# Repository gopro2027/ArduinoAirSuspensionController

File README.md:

# Open Air Suspension Management (OAS-Man)
 
<!----->

###  [  Please click here to join the Discord server](https://discord.gg/pUf7FmHKpg) 
###  [  Click here to view the comprehensive build tutorial and documentation!](https://oasman.dev)
###  [  Click here for the oasman installer/update page](https://oasman.dev/flash)

### Important Info To Potential Creators:
Please join the discord for more specific information before you built it!<br>
There may be important information to share before you begin purchasing parts.<br>

### Overview:
This is intended as a DIY replacement for products such as Airlift 3P/3H ($1500) or Airtek Stage 2+ ($1000) with a build cost of less than $500. Combined with the customizability of open sourced code, I hope this is a tempting option for some DIY-ers out there.<br>
Our goal with this project is to provide the car community with a modern fully customizable well documented air suspension system with a budget build cost in mind, all not bound by the limitations of a single company. The rest of your car is custom to you, why not your air suspension too?<br>
- Want to customize the app to match your ride? You got it.<br>
- Did your proprietary air suspension software stop working and there's no update? Not an issue here!<br>
- Sensor broke in your proprietary manifold and you have to buy a whole new one for $1000? Not an issue here, just replace the sensor for $10.<br>
- Want to use bespoke heavy duty valves but also have a nice user interface? Look no further than OAS-Man!<br>
- Control your system with a PS3/PS4/Xbox controller? Yep, [we have that](https://www.youtube.com/shorts/fbXJVwzc6P0)<br>
- Restomodding an old air suspension system? OAS-Man may be the solution!<br>
- Literally any idea you've ever wanted to try with air suspension? OASMan is the best place to start.<br>

This github repo includes an android app<sup>1</sup> and esp32 code along with some 3d printable files and a PCB. The PCB is pre-made SMD and ready for upload in JLCPCB with assembly so minimal-to-no soldering required. There is also a pre-made touch screen device you can order ($25 to $40) which is used as the dedicated controller<sup>2</sup>. There is an easy to use webpage to upload the software so there is no coding required. You will still need to supply the rest of your system which is not covered in this project, such as struts/bags, tank, compressor, tubing and fittings, ect. So that is what you would need in addition to this, similarly to what you would need for one of the on-the-shelf manifolds. If you are unsure what to purchase, I suggest referencing (or purchasing!) the [Airtekk Stage 1 Kit](https://www.airtekk.com/product-p/uni-stage1-kit.htm) as that will just about cover everything you need.<br>
<sub>1. The mobile app is behind on development and lacks various features of the controller software, and currently only has an android release. Recommended to use the touch screen controller for full functionality.</sub><br>
<sub>2. Please view the tutorial and build instructions for more info.</sub>

### Branch Information:
**main branch = ESP32** (Current full version of OASMan)<br>
**dev branch = ESP32** (Bleeding edge updates to OASMAN)<br>
**nano-v1 branch = Arduino Nano** (outdated, no longer maintained, only exists for legacy purposes)<br>
**Other branches = current dev work** (Other dev work which you can ignore)<br>
<br>
### Folder Information:
**tutorial** - Contains important build instructions (must read)<br>
**OASMan_ESP32** - The main board project<br>
**Wireless_Controller** - The project for the wireless controller of the main board<br>
**builds** - Mobile App Builds (apk's ect)<br>
**ESP32_SHARED_LIBS** - Contains files used between the main board and controller projects. Notably the config file which you may or may not need to edit.<br>
**LCDImageCreatorTool** - Code generator for making images for the tiny 128x64 screen on the manifold.<br>
**MobileApp** - New flutter mobile app using BLE (incomplete at the time of this writing)<br>
**3d Prints** - Contains files for 3d printing (more info in tutorials)<br>
**PCB** - PCB files. More info in tutorial<br>
**PS3_Controller_Tool** - Contains instructions & exe for setting the MAC address of your ps3 controller to work with OASMan<br>
**photos** - photos<br>
<br>

<br>

<!---
**Loose steps:** <br>
1. Order parts, order circuit board on JLPCB website, 3d print parts
2. Solder parts to circuit board, flip all switches to off
    1. For the manifold connector, wire the white wires (abcdefgh) in alphabetical order on the board, so 1 is a, 2 is b, and so on. The 9th wire goes to the spot right above the rest of the wires.
    2. The pressure sensors go in order... 1(manifold) -> FP (board) ... 4 -> RD. In general the order of everything is FRONT PASSENGER, REAR PASSENGER, FRONT DRIVER, REAR DRIVER abbreviatted FP, RP, FD, RD, sorry for the odd order it happened by accident
4. Configure code:
    1. get mac address of HC-06 bluetooth device by using an app or sommething to find it.
    2. Put the mac address in the android code, replacing the old mac address
    3. (Optional) Update the passwords in the app and arduino code if you want
    4. Write code to arduino
5. Circuit board single switch off, on the double switch make the top one on and bottom one off (this will power the arduino by 5v from the buck converter. 12 is bottom switch if you want to use that instead but you can ignore it)
-->

<!--

-->
<!---->
<!---->

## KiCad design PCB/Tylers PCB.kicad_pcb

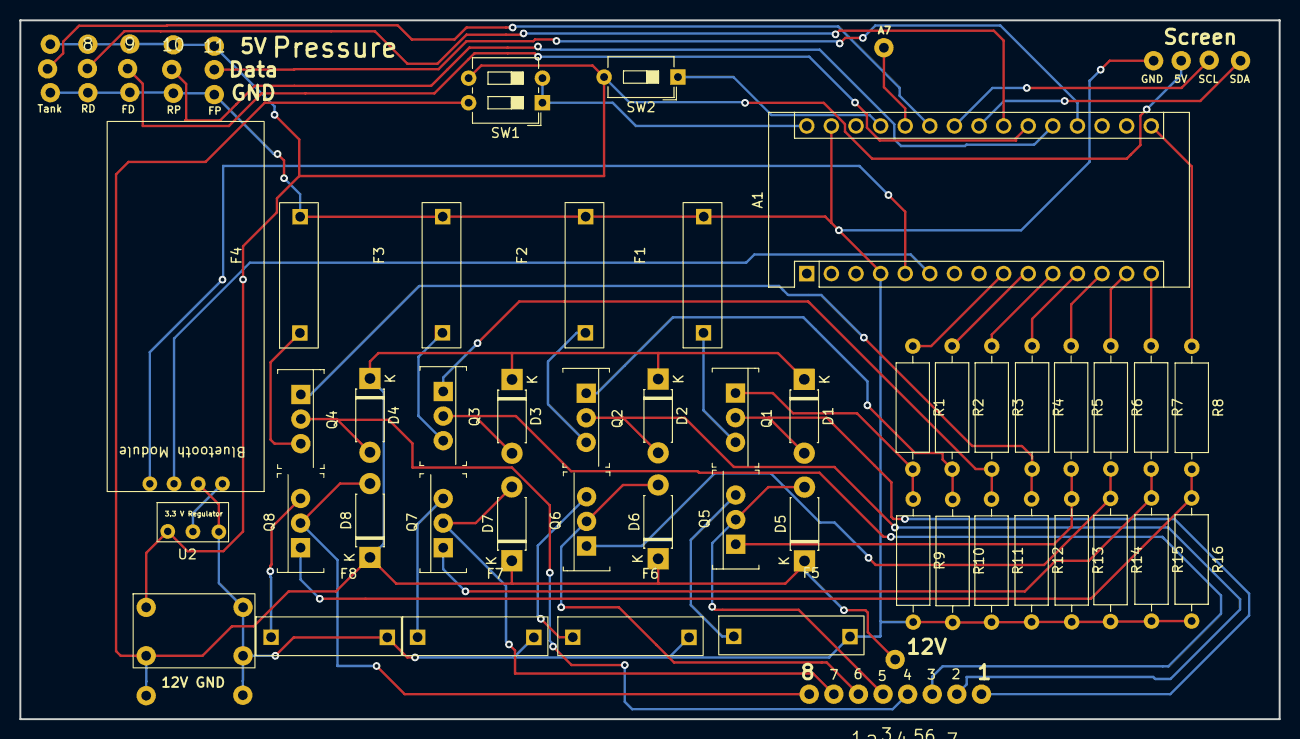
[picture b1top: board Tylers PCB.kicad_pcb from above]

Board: 2 copper layers, 130.0 x 72.1 mm, 62 parts (0 on the bottom side), 40 nets.

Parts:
1, 2, 3, 4, 5, 6, 7, 8, 9, 10, 11, 12, 13, 14, 15, 16: (no value)
3.3 V Regulator: 3.3V_regulator; 3.3V regulator
A1: Arduino_Nano_v3.x; Arduino_Nano
Bluetooth Module: DSD_Tech_Bluetooth_Module; DSD Tech Bluetooth Module
D1, D2, D3, D4, D5, D6, D7, D8: 1N4007; D_DO-41_SOD81_P7.62mm_Horizontal
F1, F2, F3, F4, F5, F6, F7, F8: 3A Fuse; 3.6x10mm
Q1, Q2, Q3, Q4, Q5, Q6, Q7, Q8: FQP30N06L; TO-220-3
R1, R2, R3, R4, R5, R6, R7, R8: R150; R_Axial_DIN0309_L9.0mm_D3.2mm_P12.70mm_Horizontal
R9, R10, R11, R12, R13, R14, R15, R16: R10K; R_Axial_DIN0309_L9.0mm_D3.2mm_P12.70mm_Horizontal
SW1: SW_DIP_x02; SW_DIP_SPSTx02_Slide_6.7x6.64mm_W7.62mm_P2.54mm_LowProfile
SW2: SW_DIP_x01; SW_DIP_SPSTx01_Slide_6.7x4.1mm_W7.62mm_P2.54mm_LowProfile
U2: DIY_More_Buck_Converter; DIY More Buck Converter

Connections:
+12V: D1.1 (K), D2.1 (K), D3.1 (K), D4.1 (K), D5.1 (K), D6.1 (K), D7.1 (K), D8.1 (K), SW1.4, U2.2 (12V_IN)
GND: 3.3 V Regulator.3 (GND), 12.1, 13.1, 14.1, 15.1, 16.1, A1.4 (GND), A1.29 (GND), Bluetooth Module.3 (GND), F1.2, F2.2, F3.2, F4.2, F5.2, F6.2, F7.2, F8.2, R9.2, R10.2, R11.2, R12.2, R13.2, R14.2, R15.2, R16.2, U2.1 (GND_IN), U2.3 (GND_OUT)
unnamed: A1.5 (D2), Bluetooth Module.1 (RX0)
unnamed: A1.6 (D3), Bluetooth Module.2 (TX0)
unnamed: A1.9 (D6), R1.1
unnamed: A1.10 (D7), R2.1
unnamed: A1.11 (D8), R3.1
unnamed: A1.12 (D9), R4.1
unnamed: A1.13 (D10), R5.1
unnamed: A1.14 (D11), R6.1
unnamed: A1.15 (D12), R7.1
unnamed: A1.16 (D13), R8.1
unnamed: A1.27 (+5V), SW2.1
unnamed: A1.30 (VIN), SW1.1, SW1.2
unnamed: F1.1, Q1.3 (S)
unnamed: F2.1, Q2.3 (S)
unnamed: F3.1, Q3.3 (S)
unnamed: F4.1, Q4.3 (S)
unnamed: F5.1, Q5.3 (S)
unnamed: F6.1, Q6.3 (S)
unnamed: F7.1, Q7.3 (S)
unnamed: F8.1, Q8.3 (S)
unnamed: Q1.1 (G), R1.2, R9.1
unnamed: Q2.1 (G), R2.2, R10.1
unnamed: Q3.1 (G), R3.2, R11.1
unnamed: Q4.1 (G), R4.2, R12.1
unnamed: Q5.1 (G), R5.2, R13.1
unnamed: Q6.1 (G), R6.2, R14.1
unnamed: Q7.1 (G), R7.2, R15.1
unnamed: Q8.1 (G), R8.2, R16.1
unnamed: 3.3 V Regulator.1 (VIN), 8.1, 9.1, 10.1, 11.1, SW1.3, SW2.2, U2.4 (5V_OUT)
unnamed: 3.3 V Regulator.2 (VOUT), Bluetooth Module.4 (VIN)
To Solenoid 1: 7.2 (D), D1.2 (A), Q1.2 (D)
To Solenoid 2: 6.2 (D), D2.2 (A), Q2.2 (D)
To Solenoid 3: 5.2 (D), D3.2 (A), Q3.2 (D)
To Solenoid 4: 4.2 (D), D4.2 (A), Q4.2 (D)
To Solenoid 5: 3.2 (D), D5.2 (A), Q5.2 (D)
To Solenoid 6: 2.2 (D), D6.2 (A), Q6.2 (D)
To Solenoid 7: 1.2 (D), D7.2 (A), Q7.2 (D)
To Solenoid 8: D8.2 (A), Q8.2 (D)

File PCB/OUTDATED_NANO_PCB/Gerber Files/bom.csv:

Designator,Footprint,Quantity,Value,LCSC Part #
15,,1,,
7,,1,,
F2,3.6x10mm,1,3A Fuse,
Q4,TO-220-3,1,FQP30N06L,FQP30N06L
13,,1,,
R1,R_Axial_DIN0309_L9.0mm_D3.2mm_P12.70mm_Horizontal,1,R150,
3.3 V Regulator,3.3V regulator,1,3.3V_regulator,
12,,1,,
_15,,1,,
9,,1,,
R4,R_Axial_DIN0309_L9.0mm_D3.2mm_P12.70mm_Horizontal,1,R150,
R14,R_Axial_DIN0309_L9.0mm_D3.2mm_P12.70mm_Horizontal,1,R10K,
Bluetooth Module,DSD Tech Bluetooth Module,1,DSD_Tech_Bluetooth_Module,
R8,R_Axial_DIN0309_L9.0mm_D3.2mm_P12.70mm_Horizontal,1,R150,
D2,D_DO-41_SOD81_P7.62mm_Horizontal,1,1N4007,
SW1,SW_DIP_SPSTx02_Slide_6.7x6.64mm_W7.62mm_P2.54mm_LowProfile,1,SW_DIP_x02,
R7,R_Axial_DIN0309_L9.0mm_D3.2mm_P12.70mm_Horizontal,1,R150,
_14,,1,,
D5,D_DO-41_SOD81_P7.62mm_Horizontal,1,1N4007,
R2,R_Axial_DIN0309_L9.0mm_D3.2mm_P12.70mm_Horizontal,1,R150,
Q8,TO-220-3,1,FQP30N06L,FQP30N06L
16,,1,,
_13,,1,,
D6,D_DO-41_SOD81_P7.62mm_Horizontal,1,1N4007,
F7,3.6x10mm,1,3A Fuse,
R5,R_Axial_DIN0309_L9.0mm_D3.2mm_P12.70mm_Horizontal,1,R150,
6,,1,,
U2,DIY More Buck Converter,1,DIY_More_Buck_Converter,
_12,,1,,
2,,1,,
R16,R_Axial_DIN0309_L9.0mm_D3.2mm_P12.70mm_Horizontal,1,R10K,
A1,Arduino_Nano,1,Arduino_Nano_v3.x,
R15,R_Axial_DIN0309_L9.0mm_D3.2mm_P12.70mm_Horizontal,1,R10K,
_11,,1,,
F3,3.6x10mm,1,3A Fuse,
_10,,1,,
_9,,1,,
R10,R_Axial_DIN0309_L9.0mm_D3.2mm_P12.70mm_Horizontal,1,R10K,
_8,,1,,
_7,,1,,
8,,1,,
Q7,TO-220-3,1,FQP30N06L,FQP30N06L
SW2,SW_DIP_SPSTx01_Slide_6.7x4.1mm_W7.62mm_P2.54mm_LowProfile,1,SW_DIP_x01,
3,,1,,
F8,3.6x10mm,1,3A Fuse,
10,,1,,
11,,1,,
R11,R_Axial_DIN0309_L9.0mm_D3.2mm_P12.70mm_Horizontal,1,R10K,
4,,1,,
D3,D_DO-41_SOD81_P7.62mm_Horizontal,1,1N4007,
F4,3.6x10mm,1,3A Fuse,
_6,,1,,
F1,3.6x10mm,1,3A Fuse,
D7,D_DO-41_SOD81_P7.62mm_Horizontal,1,1N4007,
F5,3.6x10mm,1,3A Fuse,
_5,,1,,
R6,R_Axial_DIN0309_L9.0mm_D3.2mm_P12.70mm_Horizontal,1,R150,
D8,D_DO-41_SOD81_P7.62mm_Horizontal,1,1N4007,
_4,,1,,
D1,D_DO-41_SOD81_P7.62mm_Horizontal,1,1N4007,
R3,R_Axial_DIN0309_L9.0mm_D3.2mm_P12.70mm_Horizontal,1,R150,
R13,R_Axial_DIN0309_L9.0mm_D3.2mm_P12.70mm_Horizontal,1,R10K,
_3,,1,,
Q6,TO-220-3,1,FQP30N06L,FQP30N06L
Q3,TO-220-3,1,FQP30N06L,FQP30N06L
5,,1,,
Q5,TO-220-3,1,FQP30N06L,FQP30N06L
_2,,1,,
R9,R_Axial_DIN0309_L9.0mm_D3.2mm_P12.70mm_Horizontal,1,R10K,
D4,D_DO-41_SOD81_P7.62mm_Horizontal,1,1N4007,
Q2,TO-220-3,1,FQP30N06L,FQP30N06L
,,1,,
F6,3.6x10mm,1,3A Fuse,
1,,1,,
14,,1,,
R12,R_Axial_DIN0309_L9.0mm_D3.2mm_P12.70mm_Horizontal,1,R10K,
Q1,TO-220-3,1,FQP30N06L,FQP30N06L

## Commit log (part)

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2026-01-24 Undid some comment changes that shouldn't have been comitted
2026-01-24 Cleaned up unnecessary changes in ws2p8b and ws3p5b
2026-01-24 Fix whitespace in 2p8b
2026-01-24 Moved createModernNavbar to private
2026-01-25 Removed unnecessary code that blocked -1 from clearing the selected icons
2026-01-25 reinit update for controls
    updated manual controls to work with rotation and color changes.
2026-01-25 Proper cleanup update
    Each screen properly cleans up its own objects
    ui_reinit() is clean and simple (just 3 cleanup calls)
    Adding new Options only requires updating that screen's code
2026-01-25 Made valve code better. Temporarily fixed arrows rendering
2026-01-25 Fixed memory leak with pill arrows
2026-01-25 Fixed memory leak with pill divider points
2026-01-25 Added theme color desert sand
2026-01-25 Fix for arrows looking funny
2026-01-26 removed unused code
    removed legacy control code
2026-01-26 Weird thing with ui_updateBtn
2026-01-26 Added a bit extra safety to the option class even though unnecessary
2026-01-26 Fixed animation for 2p8b by adding LV_USE_STDLIB_MALLOC=LV_STDLIB_CLIB
2026-01-26 Changed 2p8b to be double buffered partial render
2026-01-26 Cleaned up duplicate code on ui_scrPresets.cpp
2026-01-28 Removed unused ui helpers
2026-01-29 Fix for navbar callbacks
2026-01-29 added animated navbar underline
2026-01-30 update for statusbar information
2026-01-30 Added led code
2026-02-03 New car creator program
2026-02-03 More updates to custom car image maker
2026-02-03 Made the program better
2026-02-03 Reverted formatting changes because I know it's gonna give us some merge conflicts later if I don't
2026-02-05 Added manifold decorative plate
2026-02-06 Update for statusbar/Post-reload
    Added new brightness_slider_released_cb that calls setbrightness()
    Added bool animate = true parameter to changeScreen() (default preserves existing behavior)
    ui_reinit() now calls changeScreen(prevScreen, false) — instant page switch after reload
2026-02-11 Removed some laggy animations
    status bar dropdown and pill resizing
2026-02-19 Turn off 6 valve manifold
2026-02-19 Changed color to dark cyan
2026-02-20 Added adsD and auto switch tank sensor to it if it exists
2026-02-20 Added isVehicleParked function
    GPS code for it isn't finished yet though, but I will use this function to update other features safety.
2026-02-20 Implemented isVehicleParked in a few spots where it was needed
    Still need to implement isVehicleParked on the videogame controller
2026-02-21 Fixed car rendering position
2026-02-21 Fixed 2.8b backlight
2026-02-21 added SIX_VALVE_MANIFOLD_OPEN_TANK_VALVE_WHEN_COMPRESSOR_IS_RUNNING
    Should only be used as directed in the user_defines.h
2026-03-01 First pass of code, need to test and clean up bugs
2026-03-01 Bug on frontend didn't set default value of on off properly
2026-03-02 Hide height sensor toggleable values when not selected
2026-03-02 magic number wheel nums
2026-03-02 Initial cleanup of these status packets into a config bittset
    Hasn't been tested yet at all. Needs testing of all 6 of these functions before it can be moved along.
2026-03-02 Updated gfx library version to 1.6.5 in hopes it fixed the incompatability with latest version of arduino-esp32
    I'm not entirely sure why it's downloading a new version of arduino esp32 and not using a fixed verssion, but not looking into that right now. Here is a github issue of the error for reference: https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
2026-03-02 Fix for new core version in nimble
2026-03-06 Fix for six valve manifold to force the compressor (and tank valve) off when tank output is opened
2026-03-06 Updated mobile app with new bluetooth code
2026-03-06 Initial commit. Has some UI issues
2026-03-29 Auxillary code WIP NOT FINISHED
    Should have the first few functions working on timing
    have not added anything to the controller side yet.
    Needs changed to be a bittset of functions that are stored, and the first 2 manual functions are called statefully instead of being stored as a setting.
2026-03-29 removed device libs from search exclude
2026-04-02 Added initial upload for knob device support
    https://www.waveshare.com/wiki/ESP32-S3-Knob-Touch-LCD-1.8
2026-04-02 First version of settings for circle screen ui
2026-04-02 Okay finished first ui for circle screen.
2026-04-03 Home screen circle glow
2026-04-03 Removed glow and replaced with simple color change
2026-04-03 Slight speed improvement in circular screen driver. Changes partial lines flush to 24 from 16 and 20
2026-04-03 Updates to preset page
2026-04-03 Moved preset button to center of home screen
2026-04-03 Updates to the UI on the home page with the preset button
2026-04-03 Fixed button press bug on air out, inverted arc so they all fill upwards
2026-04-03 added preset number to help with feedback when loading a new preset
    The preset would otherwise be 'hidden' so this helps at least show it if we swap to a different preset
2026-04-03 added the knob to the build
2026-04-03 Added rotary guage to the website
2026-04-05 Updated packet format in flutter app and made it save upon edit
    also updated the manifold so that in the config packet if i set the values, it will update all connected controllers
2026-04-05 Updated names of settings to match the controller
2026-04-05 Added more of the settings from the controller to the mobile app
2026-04-05 Fixed direct download when proxy is rate limited
    This fixes the -5 error i was getting at times.
    Summary of fix:
    Moved wificlientsecure to global scope. https stores a copy of this object, so wanted to make sure it sticks around
    Also make the https object into a pointer, so i can delete it to fix the later issue that happens if we try to reuuse https as http.
2026-04-05 Fixed slight typo
2026-04-05 Added a switch to go from stream to non-stream on json response
    Mainly because on the controller if we run on the github direct it sometimes responds in chunked format which the streamed version is not a fan of trying to parse, so then we retry with the non-strea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
2026-04-05 Added privacy policy to mobile app settings
2026-04-07 Temporary fix for 3.5 and update nimble to 2.5.0
2026-04-07 Clean up some of the unnecessary code on the statusbar
2026-04-07 undid a useless code change
2026-04-09 Moved auxillary output mode to config values packet and added manual control packet
2026-04-09 Added internal setting to auxillary output
2026-04-10 Removed detect pressure sensors, and fixed image picker permission bug
2026-04-10 Fixed app name and icon
2026-04-10 Fixed website link button
2026-04-10 Improved performance on settings page
2026-04-10 updated _readOnlyStatusRow to wrap gracefully
2026-04-14 Added deciseconds to auxillary output settings
2026-04-17 Improved setup code in the settings and added auxillary output page
2026-04-27 Removed commented out code
2026-05-15 Added auxillary settings to mobile app
2026-05-15 Fixed valve mask on axle up down mobileapp
2026-05-15 Fixed up down axle bug
2026-05-15 Added auxillary settings to mobileapp
2026-05-15 Fixed graphical error on selected item in settings dropdown on controller
2026-05-15 Fixed bug where you could click behind dialogs
2026-05-15 Disabled triangle icon in statusbar until we decide to wire it up to something more important
2026-05-15 Made oled screen address save into nvs for people with odd screen addresses
2026-05-17 4.0 Board update
    4.0 PCB complete update. Corrected zener and silk screen error.
2026-05-18 4.0.1 HotFix
    4.0 Board corrections updated to 4.0.1 HotFix
2026-05-18 Config packet issue fix
    Sometimes when saving a preset the config packet saves bad data from the stack to the board. This ensures that does not happen.
2026-05-19 Significantly simplified ota updates by moving almost all the code into the cloudflare worker
2026-05-19 Cloudflare worker will now delete the cache of all the binaries if a new release json version is found
2026-05-19 Fixed a bug with short overflow.
2026-05-19 Updated actions script to be compatable with node 24
    This is untested code. Github says june 2nd they are upgrading to node 24 though
2026-05-19 fix: V-001 security vulnerability
    Automated security fix generated by OrbisAI Security
2026-05-19 temporarily removed most for build test
2026-05-19 Revert "temporarily removed most for build test"
    This reverts commit 26e48c4e61cf8bbefe60280e41d3bee1b5e637a0.
2026-05-19 fix: V-006 security vulnerability
    Automated security fix generated by OrbisAI Security
2026-05-19 Moved this code into the isAuthed
    It doesn't technically cause an issue, but that code would get ran by an unauthorized device. All it would do is simply copy possible stack values to the valveControlBittsetArr... maybe. Either way, 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
2026-05-21 Support for pwm dutycycle to the solenoid class with 10hz frequency set globally by default
2026-05-21 Added test 50% dutycycle
2026-06-06 untested ai code improvemented
2026-06-06 Added claude code agents
2026-06-06 improved claude.md
2026-06-11 Tap on dim screen will no longer execute item on screen
    Also set minimum screen timeout to 5s
2026-06-11 Build fix for 2.8
2026-06-11 accidental
2026-06-13 Increased fps on 3p5 to 60 at idle
2026-06-16 Restructured memory on ws2p8b
    1. ws2p8b had lv malloc set to CLIB (standard malloc() function), so removed that and now have it set back to BUILTIN (finds space in LV_MEM_SIZE array instead of malloc) like the other devices
    2. Then defined LV_MEM_POOL_ALLOC via the new LV_MEM_POOL_PSRAM flag so that the alloc for BUILTIN will alloc within psram (heap_caps_malloc(size, MALLOC_CAP_SPIRAM))
    3. now that the builtin mallocs are in psram which has more memory, increase mem size to 512
2026-06-17 Updated the flash page to be a react app
2026-06-17 Added some extra features to the flash page
2026-06-17 dependabot issue discovered within the new flash page.
    Not necessarily a real security issue because of how we do things, but still
2026-06-18 Converted the car creator script for controllers into a web thing
2026-06-19 First version of the custom car image uploading
2026-06-19 Made steps a lot easier for controller car creator
2026-06-19 Removed unnecessary import
2026-06-19 AI disclaimer
2026-06-19 More info to ai disclaimer on the car storage and car serial retreival files
2026-06-19 Made wheel wells not render when using custom car image
2026-06-19 testing spiffs issue fix
2026-06-19 Undid main.yml change
2026-06-19 only 3.5b will compile
2026-06-21 Improved image loading greatly
2026-06-21 Fixed partition text for 2.8
2026-06-21 Revert "Merge branch 'dev' of https://github.com/gopro2027/ArduinoAirSuspensionController into dev"
    This reverts commit 3c89725842e01fcda01f43f3b695e9d12fff62eb, reversing
    changes made to 94df349857041123678a0065d8371f2ecc592e42.
2026-06-21 added link for controller car creator
2026-06-21 Removed cdc on boot to fix the 3.5 devices
2026-06-29 initial commit, works on presets (untested)
2026-06-29 added the baseline function which captures all valve openings
    removed quick mode code
2026-06-29 Removed lookup table and replaced with simple y=10x equation which almost perfectly matches the lookup table
2026-06-29 adjusted isVehicleParked
2026-06-30 Hopefully fixed the logic a bit for the height sensorless levelling
    Fixed bug with stableSince only setting once, and not always resetting every time it drifts
    Check if baseline is captured to actually execute the levelling (was missing before!)
    added nullifySensorlessBaseline to goalRoutine to make sure it gets reset on a goal 100% for sure
    made isActive check if inside a goalRoutine
2026-06-30 updated maintain pressure to use the new more broad pressure tracker value we added
2026-06-30 Made maintain preset up only
